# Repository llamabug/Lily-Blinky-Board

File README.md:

# Lily-Blinky-Board
My first hardware! A blinky board in the custom shape of a lily (my favourite flower!)  🪷
<br>
I wanted to get into hardware, and this was kind of the perfect first project as it was easy to follow but introduced my to quite a few different skills- creating PCBs, soldering. 

This project features 10 LED lights that blink in sequence, and was made in KICAD from a Hack Club Stasis tutorial.
<br> It also uses a NE555P timer, a 4017, a Conn_01x02Socket and multiple capacitators/resistors (I believe there is a kit for these?). 
<br>As my first hardware project, it was pretty difficult, especially with the DXF files, but I am really proud of the final result, and it was pretty fun to make, so I will almost certainly be building more hardware in the future.

<h3>Build Journey!</h3>

<br>
I built the board in KICAD, and created a custom border and silkscreen to make it look more like a lily. As I mentioned in my stasis journal this took a long time to sort through the DXF file, but the wiring diagrams and schematics weren't too hard to figure out
<br><br>

<br>
Soldering took two attempts, as it was my first time, and the first one ended up pretty messy and didn't work. However, the second time I figured out what went wrong beforehand and was able to solder it a whole lot better than the first attempt.  It was very exciting connecting the battery and seeing the board light up!
This project is pretty much just the board + soldered components, no case or anything made here :)

<h3>BOM</h3>
Custom PCB -  -  -  - From JLCPCB -  -  -  - $2.30USD
<br>
Blinky Board Kit -  -  -  - Hackclub HQ? -  -  -  - [no price]

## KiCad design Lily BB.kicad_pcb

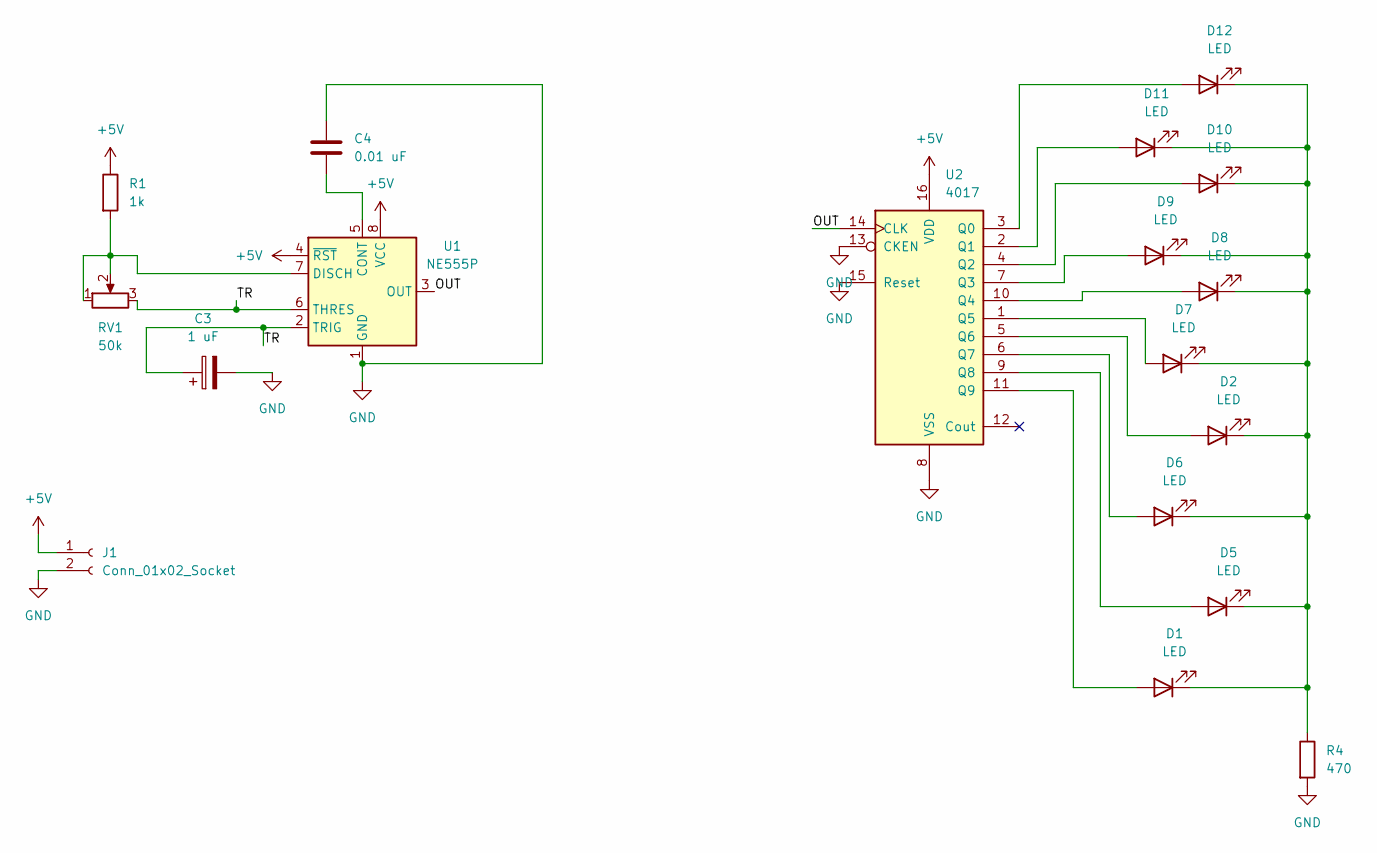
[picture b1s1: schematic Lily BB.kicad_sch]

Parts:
C3: 1 uF; CP_Radial_D5.0mm_P2.00mm
C4: 0.01 uF; C_Disc_D7.5mm_W2.5mm_P5.00mm
D1, D2, D5, D6, D7, D8, D9, D10, D11, D12: LED; LED_D3.0mm
J1: Conn_01x02_Socket; PinHeader_1x02_P2.54mm_Vertical
R1: 1k; R_Axial_DIN0207_L6.3mm_D2.5mm_P7.62mm_Horizontal
R4: 470; R_Axial_DIN0207_L6.3mm_D2.5mm_P7.62mm_Horizontal
RV1: 50k; Potentiometer_Vishay_T93YA_Vertical
U1: NE555P; DIP-8_W7.62mm
U2: 4017; DIP-16_W7.62mm

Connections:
+5V: J1.1, R1.1, U1.4 (~RST), U1.8 (VCC), U2.16 (VDD)
/OUT: U1.3 (OUT), U2.14 (CLK)
/TR: C3.1, RV1.3, U1.2 (TRIG), U1.6 (THRES)
GND: C3.2, C4.1, J1.2, R4.2, U1.1 (GND), U2.8 (VSS), U2.13 (CKEN), U2.15 (Reset)
unnamed: D1.2 (A), U2.11 (Q9)
unnamed: D1.1 (K), D2.1 (K), D5.1 (K), D6.1 (K), D7.1 (K), D8.1 (K), D9.1 (K), D10.1 (K), D11.1 (K), D12.1 (K), R4.1
unnamed: D2.2 (A), U2.5 (Q6)
unnamed: D5.2 (A), U2.9 (Q8)
unnamed: D6.2 (A), U2.6 (Q7)
unnamed: D7.2 (A), U2.1 (Q5)
unnamed: D8.2 (A), U2.10 (Q4)
unnamed: D9.2 (A), U2.7 (Q3)
unnamed: D10.2 (A), U2.4 (Q2)
unnamed: D11.2 (A), U2.2 (Q1)
unnamed: D12.2 (A), U2.3 (Q0)
unnamed: C4.2, U1.5 (CONT)
unnamed: R1.2, RV1.1, RV1.2, U1.7 (DISCH)

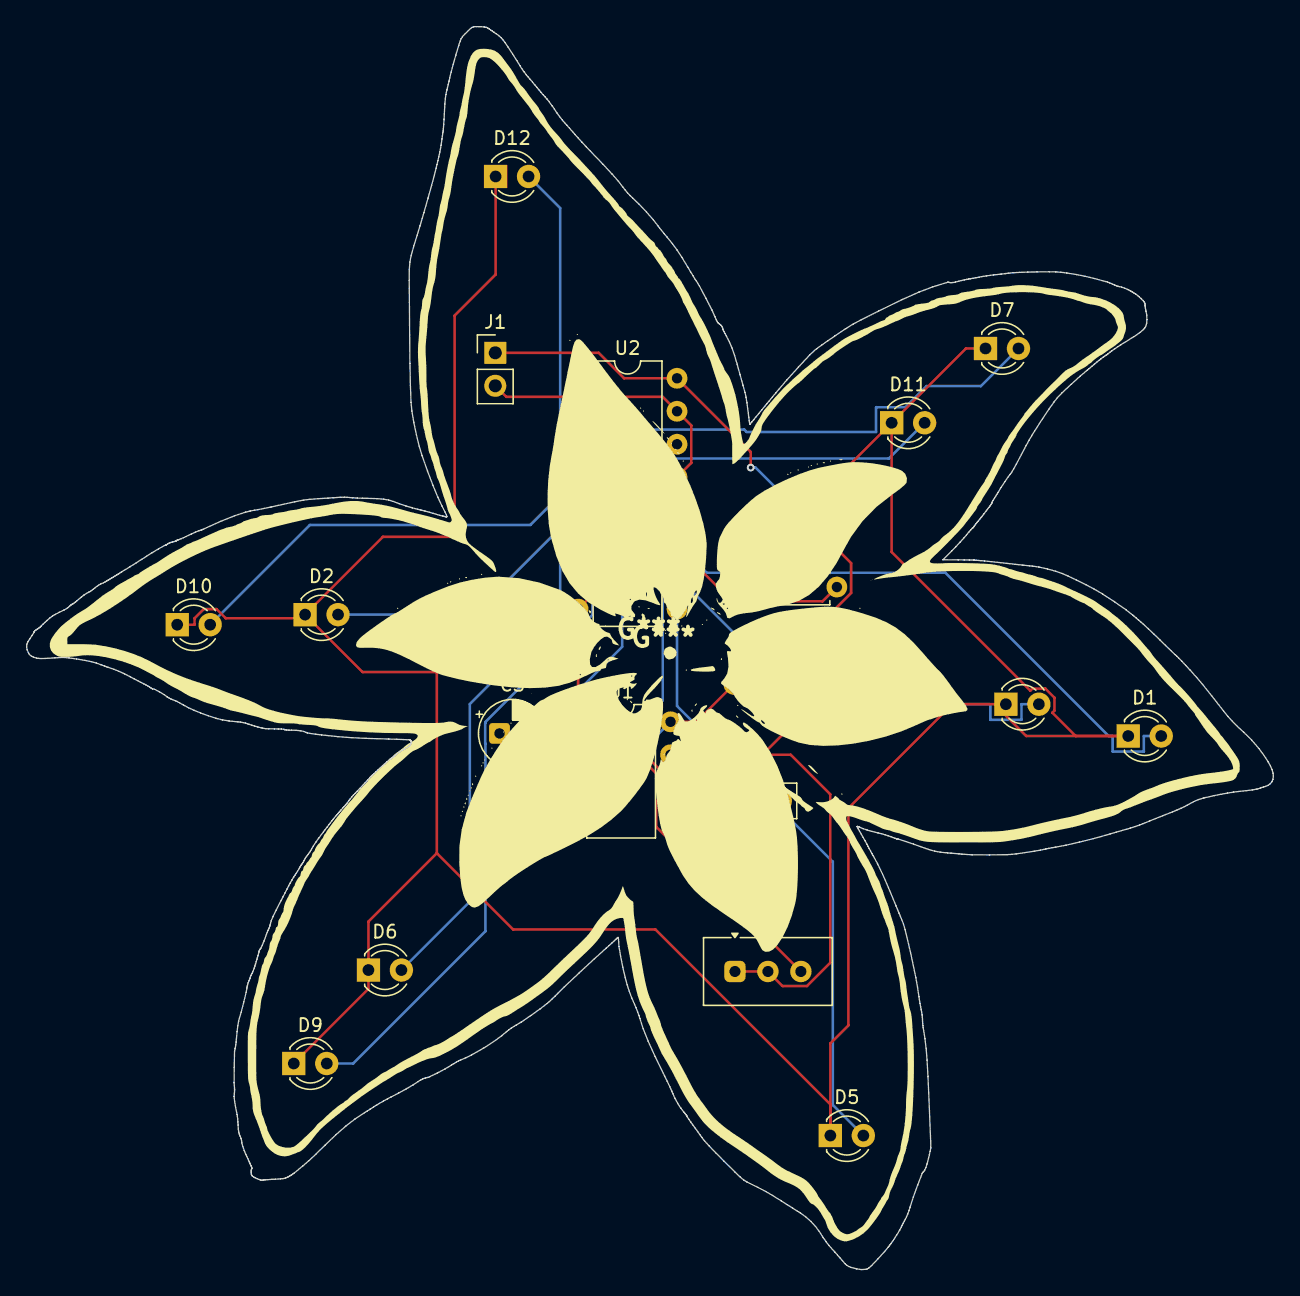
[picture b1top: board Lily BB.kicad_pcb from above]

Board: 2 copper layers, 96.0 x 95.7 mm, 18 parts (0 on the bottom side), 17 nets.
